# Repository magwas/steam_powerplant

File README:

An Open Hardware RISC-V based rugged, watercooled laptop with steampunk design.

Design Goals:

- based on the HiFive Unmatched Rev B board, because it is RISC-V
- actually useable
- waterproof
- shock proof
- long battery life
- water cooled
- steampunk

Not Design Goals:

- small
- lightweight

I wanted a RISC-V laptop. 
I usually carry my laptop in my car, and sometimes things happen to it.
So I choose ruggedness over lightness.
The laptop is my single most important object, so I looked up the parts I need, without regard to their price.
Well, later I added up the prices, and got a little shock.
But I have already ordered everything, so...

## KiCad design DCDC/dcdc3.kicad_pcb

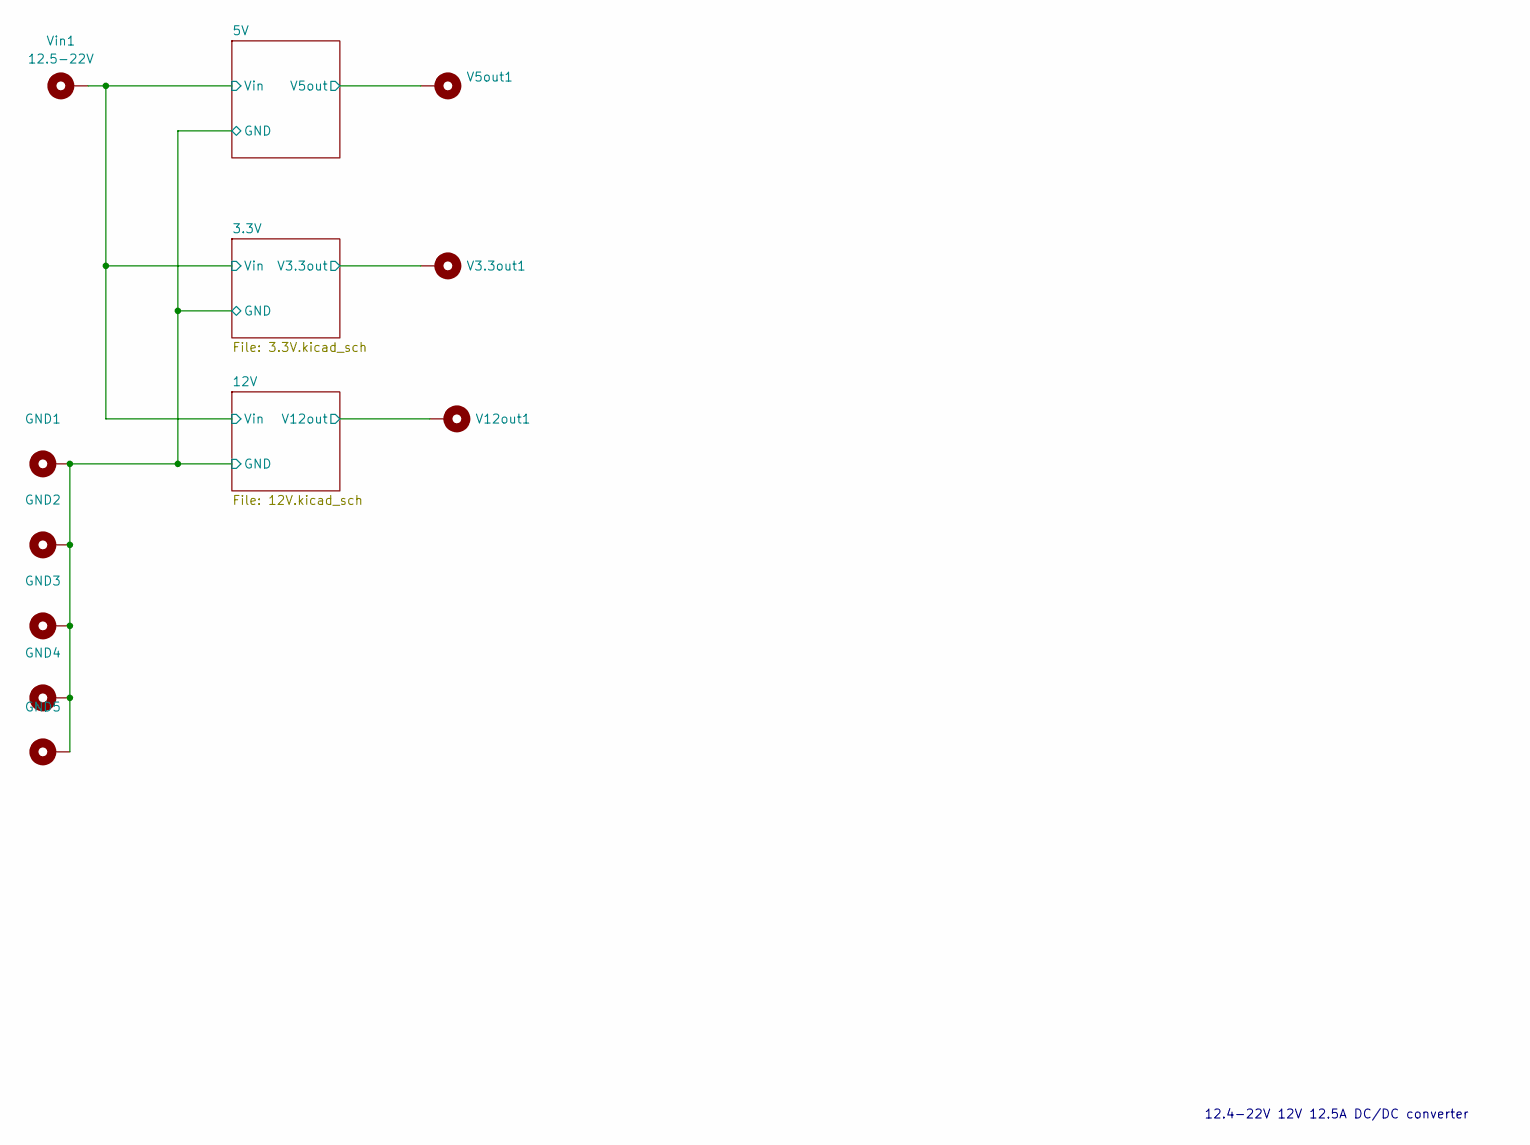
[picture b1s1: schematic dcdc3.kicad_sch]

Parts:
GND1, GND2, GND3, GND4, GND5: MountingHole_2.7mm_M2.5_Pad_Via
V3.3out1, V5out1, V12out1: MountingHole_2.7mm_M2.5_Pad_Via
Vin1: 12.5-22V; MountingHole_2.7mm_M2.5_Pad_Via

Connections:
/3.3V/V3.3out: V3.3out1.1; also elsewhere on the board
/5V/V5out: V5out1.1; also elsewhere on the board
/12V/GND: GND1.1, GND2.1, GND3.1, GND4.1, GND5.1; also elsewhere on the board
/12V/V12out: V12out1.1; also elsewhere on the board
/12V/Vin: Vin1.1; also elsewhere on the board

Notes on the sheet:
12.4-22V 12V 12.5A DC/DC converter

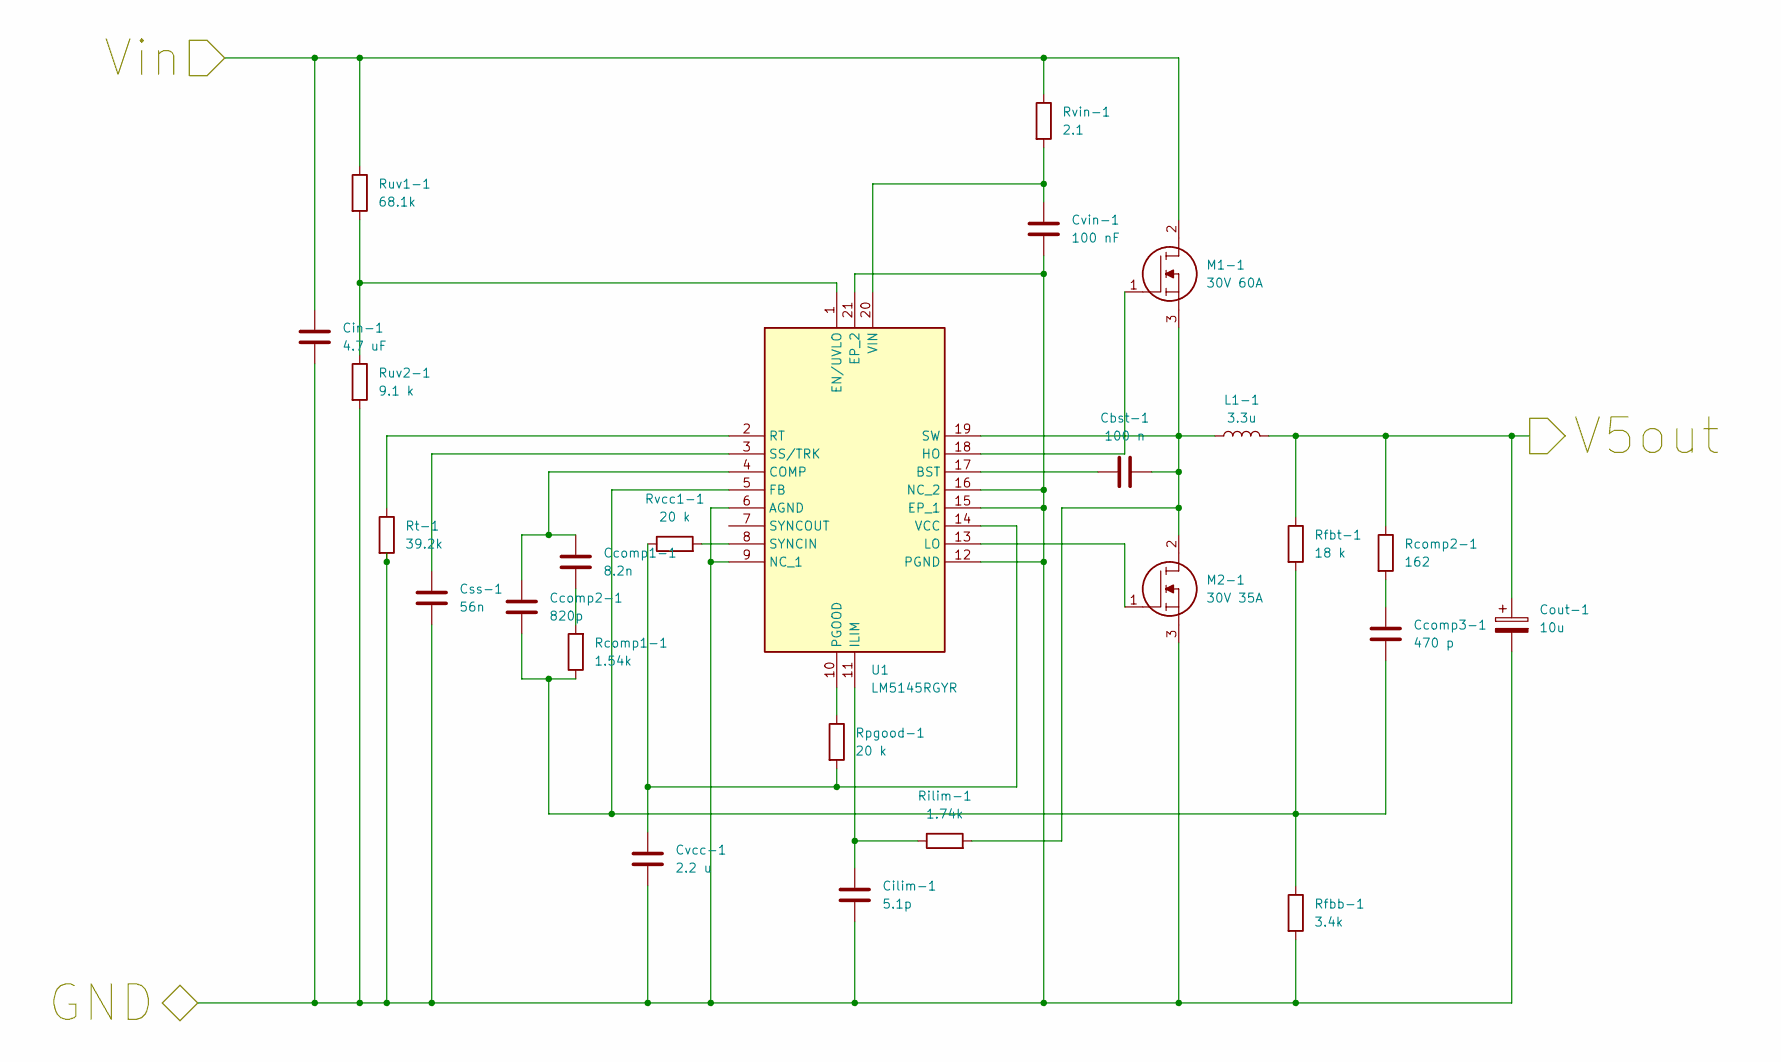
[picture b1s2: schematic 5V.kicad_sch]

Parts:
Cbst-1: 100 n; C_0603_1608Metric; Manufacturer_Part_Number C0603C104J1RACAUTO
Ccomp1-1: 8.2n; C_0402_1005Metric; Manufacturer_Part_Number GRM155R71C822KA01D
Ccomp2-1: 820p; C_0402_1005Metric; Manufacturer_Part_Number GRM155R71H821KA01D
Ccomp3-1: 470 p; C_0402_1005Metric; Manufacturer_Part_Number CGA2B2X7R1H471K050BA
Cilim-1: 5.1p; C_0805_2012Metric; Manufacturer_Part_Number C0805C519DBGACTU
Cin-1: 4.7 uF; C_1210_3225Metric; Manufacturer_Part_Number GRM32ER71H475KA88L
Cout-1: 10u; C_Radial_D10.0mm_H12.5mm_P5.00mm; Manufacturer_Part_Number KTD500B106M55A0T00
Css-1: 56n; C_0402_1005Metric; Manufacturer_Part_Number GRM155R71C563KA88D
Cvcc-1: 2.2 u; C_0402_1005Metric; Manufacturer_Part_Number C1005X5R1V225K050BC
Cvin-1: 100 nF; C_0603_1608Metric; Manufacturer_Part_Number CGA3E2X7R1H104K080AA
L1-1: 3.3u; A3mmCoil; Manufacturer_Part_Number D=15mm,N=15,L=15mm,d=2mm
M1-1: 30V 60A; TO545P521X1594X2566-3P; Mouser Part Number 747-IXFX360N10T
M2-1: 30V 35A; TO545P521X1594X2566-3P; Mouser Part Number 747-IXFX360N10T
Rcomp1-1: 1.54k; R_0402_1005Metric; Manufacturer_Part_Number CRCW04021K78FKED
Rcomp2-1: 162; R_0402_1005Metric; Manufacturer_Part_Number CRCW0402162RFKED
Rfbb-1: 3.4k; R_0402_1005Metric; Manufacturer_Part_Number CRCW04023K40FKED
Rfbt-1: 18 k; R_0603_1608Metric; Manufacturer_Part_Number RC0603FR-0718KL
Rilim-1: 1.74k; R_0402_1005Metric; Manufacturer_Part_Number CRCW04021K74FKED
Rpgood-1: 20 k; R_0603_1608Metric; Manufacturer_Part_Number RC0603FR-0720KL
Rt-1: 39.2k; R_0402_1005Metric; Manufacturer_Part_Number CRCW040239K2FKED
Ruv1-1: 68.1k; R_0603_1608Metric; Manufacturer_Part_Number ERA-3VEB6812V
Ruv2-1: 9.1 k; R_0603_1608Metric; Manufacturer_Part_Number RC0603FR-079K1L
Rvcc1-1: 20 k; R_0603_1608Metric; Manufacturer_Part_Number RC0603FR-0720KL
Rvin-1: 2.1; R_0603_1608Metric; Manufacturer_Part_Number CRCW06032R10FKEA
U1: LM5145RGYR; RGY0020B; Manufacturer_Part_Number LM5145RGYR; Mouser Part Number 595-LM5145RGYR

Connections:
/5V/V5out: Cout-1.1, L1-1.2, Rcomp2-1.1, Rfbt-1.1; also elsewhere on the board
/12V/GND: Cilim-1.2, Cin-1.2, Cout-1.2, Css-1.2, Cvcc-1.2, Cvin-1.2, M2-1.3, Rfbb-1.2, Rt-1.2, Ruv2-1.2, U1.6 (AGND), U1.9 (NC_1), U1.12 (PGND), U1.15 (EP_1), U1.16 (NC_2), U1.21 (EP_2); also elsewhere on the board
/12V/Vin: Cin-1.1, M1-1.2, Ruv1-1.1, Rvin-1.1; also elsewhere on the board
unnamed: Ccomp1-1.1, Rcomp1-1.2
unnamed: Ccomp3-1.1, Rcomp2-1.2
unnamed: Cbst-1.1, U1.17 (BST)
unnamed: Ccomp1-1.2, Ccomp2-1.2, U1.4 (COMP)
unnamed: Ruv1-1.2, Ruv2-1.1, U1.1 (EN/UVLO)
unnamed: Ccomp2-1.1, Ccomp3-1.2, Rcomp1-1.1, Rfbb-1.1, Rfbt-1.2, U1.5 (FB)
unnamed: M1-1.1, U1.18 (HO)
unnamed: Cilim-1.1, Rilim-1.1, U1.11 (ILIM)
unnamed: M2-1.1, U1.13 (LO)
unnamed: Rpgood-1.1, U1.10 (PGOOD)
unnamed: Rt-1.1, U1.2 (RT)
unnamed: Css-1.1, U1.3 (SS/TRK)
unnamed: Cbst-1.2, L1-1.1, M1-1.3, M2-1.2, Rilim-1.2, U1.19 (SW)
unnamed: Rvcc1-1.2, U1.8 (SYNCIN)
unnamed: Cvcc-1.1, Rpgood-1.2, Rvcc1-1.1, U1.14 (VCC)
unnamed: Cvin-1.1, Rvin-1.2, U1.20 (VIN)

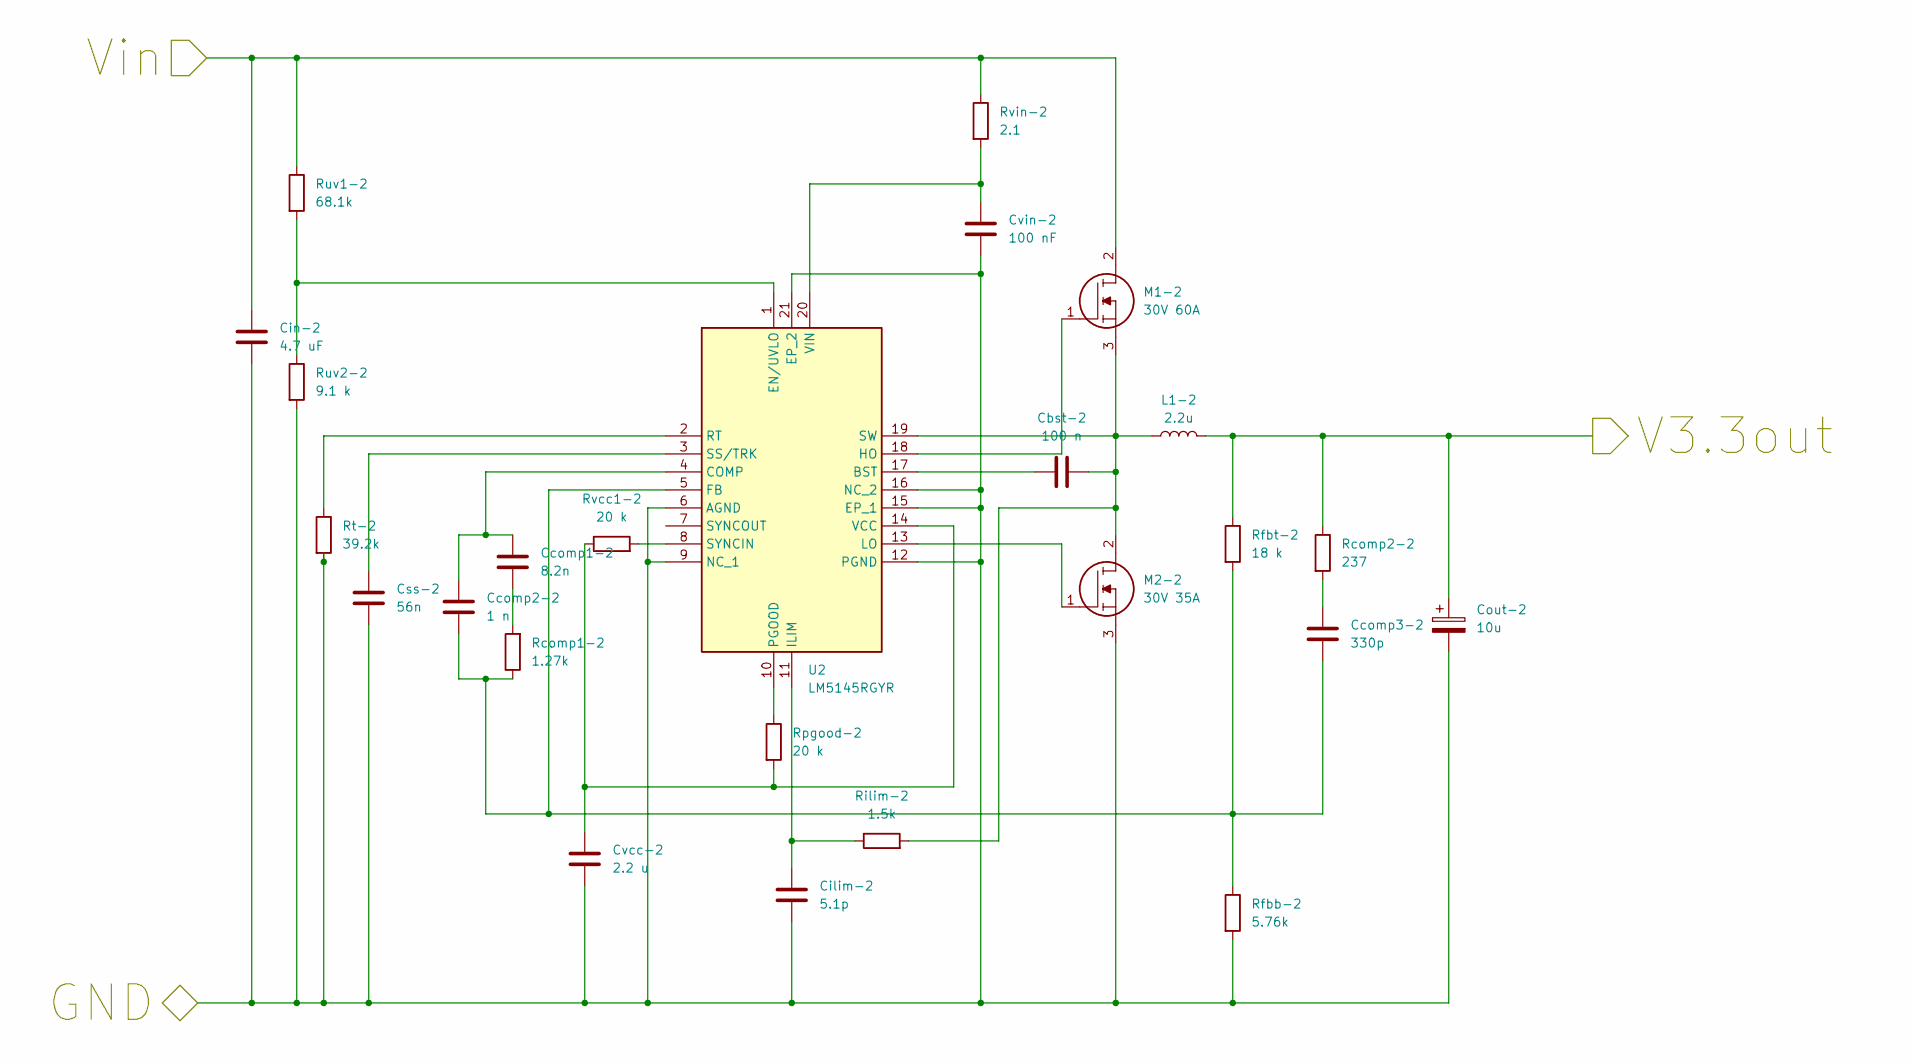
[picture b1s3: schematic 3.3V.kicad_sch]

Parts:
Cbst-2: 100 n; C_0603_1608Metric; Manufacturer_Part_Number C0603C104J1RACAUTO
Ccomp1-2: 8.2n; C_0402_1005Metric; Manufacturer_Part_Number GRM155R71C822KA01D
Ccomp2-2: 1 n; C_0402_1005Metric; Manufacturer_Part_Number GRM155R71C102KA01D
Ccomp3-2: 330p; C_0402_1005Metric; Manufacturer_Part_Number CGA2B2X7R1H331K050BA
Cilim-2: 5.1p; C_0805_2012Metric; Manufacturer_Part_Number C0805C519DBGACTU
Cin-2: 4.7 uF; C_1210_3225Metric; Manufacturer_Part_Number GRM32ER71H475KA88L
Cout-2: 10u; C_Radial_D10.0mm_H12.5mm_P5.00mm; Manufacturer_Part_Number KTD500B106M55A0T00
Css-2: 56n; C_0402_1005Metric; Manufacturer_Part_Number GRM155R71C563KA88D
Cvcc-2: 2.2 u; C_0402_1005Metric; Manufacturer_Part_Number C1005X5R1V225K050BC
Cvin-2: 100 nF; C_0603_1608Metric; Manufacturer_Part_Number CGA3E2X7R1H104K080AA
L1-2: 2.2u; A3mmCoil; Manufacturer_Part_Number D=15mm,N=10,L=20mm,d=2mm
M1-2: 30V 60A; TO545P521X1594X2566-3P; Mouser Part Number 747-IXFX360N10T
M2-2: 30V 35A; TO545P521X1594X2566-3P; Mouser Part Number 747-IXFX360N10T
Rcomp1-2: 1.27k; R_0402_1005Metric; Manufacturer_Part_Number CRCW04021K27FKED
Rcomp2-2: 237; R_0402_1005Metric; Manufacturer_Part_Number CRCW0402237RFKED
Rfbb-2: 5.76k; R_0402_1005Metric; Manufacturer_Part_Number CRCW04025K76FKED
Rfbt-2: 18 k; R_0603_1608Metric; Manufacturer_Part_Number RC0603FR-0718KL
Rilim-2: 1.5k; R_0402_1005Metric; Manufacturer_Part_Number CRCW04021K50FKED
Rpgood-2: 20 k; R_0603_1608Metric; Manufacturer_Part_Number RC0603FR-0720KL
Rt-2: 39.2k; R_0402_1005Metric; Manufacturer_Part_Number CRCW040239K2FKED
Ruv1-2: 68.1k; R_0603_1608Metric; Manufacturer_Part_Number ERA-3VEB6812V
Ruv2-2: 9.1 k; R_0603_1608Metric; Manufacturer_Part_Number RC0603FR-079K1L
Rvcc1-2: 20 k; R_0603_1608Metric; Manufacturer_Part_Number RC0603FR-0720KL
Rvin-2: 2.1; R_0603_1608Metric; Manufacturer_Part_Number CRCW06032R10FKEA
U2: LM5145RGYR; RGY0020B; Manufacturer_Part_Number LM5145RGYR; Mouser Part Number 595-LM5145RGYR

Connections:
/3.3V/V3.3out: Cout-2.1, L1-2.2, Rcomp2-2.1, Rfbt-2.1; also elsewhere on the board
/12V/GND: Cilim-2.2, Cin-2.2, Cout-2.2, Css-2.2, Cvcc-2.2, Cvin-2.2, M2-2.3, Rfbb-2.2, Rt-2.2, Ruv2-2.2, U2.6 (AGND), U2.9 (NC_1), U2.12 (PGND), U2.15 (EP_1), U2.16 (NC_2), U2.21 (EP_2); also elsewhere on the board
/12V/Vin: Cin-2.1, M1-2.2, Ruv1-2.1, Rvin-2.1; also elsewhere on the board
unnamed: Ccomp1-2.1, Rcomp1-2.2
unnamed: Ccomp3-2.1, Rcomp2-2.2
unnamed: Cbst-2.1, U2.17 (BST)
unnamed: Ccomp1-2.2, Ccomp2-2.2, U2.4 (COMP)
unnamed: Ruv1-2.2, Ruv2-2.1, U2.1 (EN/UVLO)
unnamed: Ccomp2-2.1, Ccomp3-2.2, Rcomp1-2.1, Rfbb-2.1, Rfbt-2.2, U2.5 (FB)
unnamed: M1-2.1, U2.18 (HO)
unnamed: Cilim-2.1, Rilim-2.1, U2.11 (ILIM)
unnamed: M2-2.1, U2.13 (LO)
unnamed: Rpgood-2.1, U2.10 (PGOOD)
unnamed: Rt-2.1, U2.2 (RT)
unnamed: Css-2.1, U2.3 (SS/TRK)
unnamed: Cbst-2.2, L1-2.1, M1-2.3, M2-2.2, Rilim-2.2, U2.19 (SW)
unnamed: Rvcc1-2.2, U2.8 (SYNCIN)
unnamed: Cvcc-2.1, Rpgood-2.2, Rvcc1-2.1, U2.14 (VCC)
unnamed: Cvin-2.1, Rvin-2.2, U2.20 (VIN)

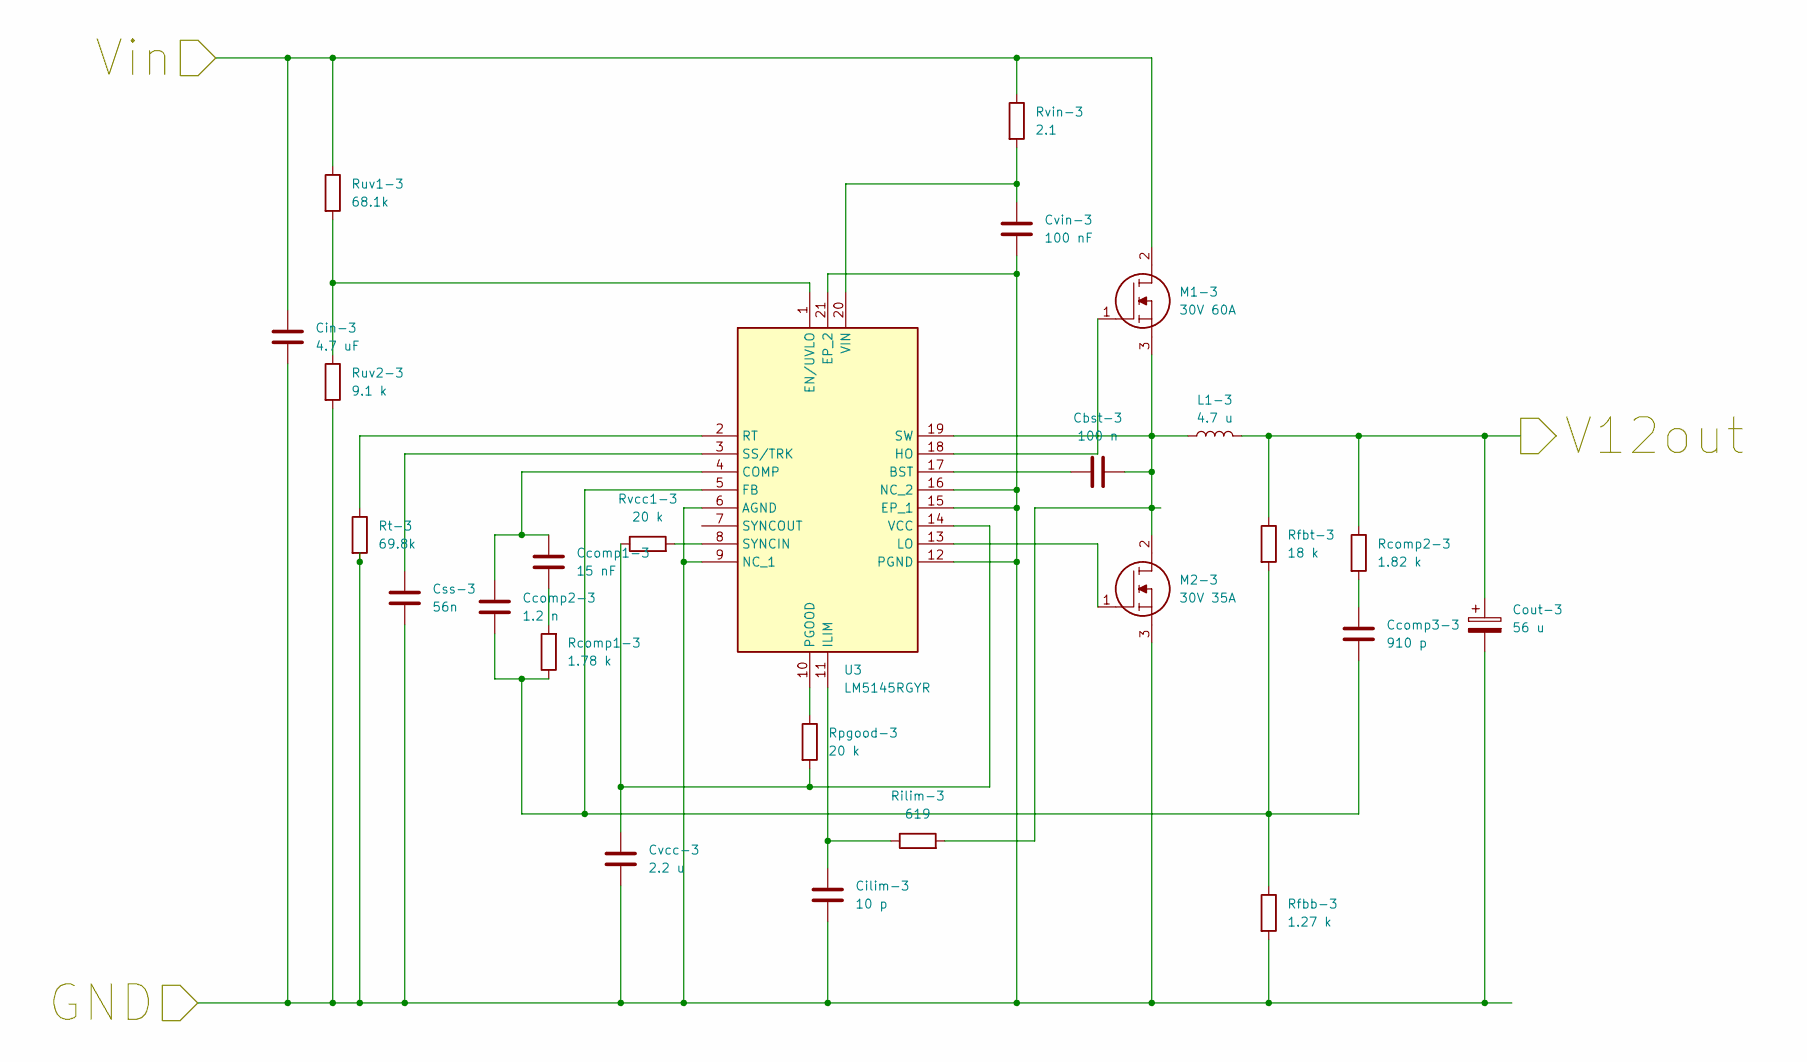
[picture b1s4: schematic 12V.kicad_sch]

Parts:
Cbst-3: 100 n; C_0603_1608Metric; Manufacturer_Part_Number C0603C104J1RACAUTO
Ccomp1-3: 15 nF; C_0402_1005Metric; Manufacturer_Part_Number GRM155R71C153KA01D
Ccomp2-3: 1.2 n; C_0402_1005Metric; Manufacturer_Part_Number GRM155R71H122KA01D
Ccomp3-3: 910 p; C_0402_1005Metric; Manufacturer_Part_Number GRM1555C1H911JA01D
Cilim-3: 10 p; C_0603_1608Metric; Manufacturer_Part_Number GRM1885C2A100JA01D
Cin-3: 4.7 uF; C_1210_3225Metric; Manufacturer_Part_Number GRM32ER71H475KA88L
Cout-3: 56 u; C_Radial_D6.3mm_H5.0mm_P2.50mm; Manufacturer_Part_Number APSG250ELL560MF05S
Css-3: 56n; C_0402_1005Metric; Manufacturer_Part_Number GRM155R71C563KA88D
Cvcc-3: 2.2 u; C_0402_1005Metric; Manufacturer_Part_Number C1005X5R1V225K050BC
Cvin-3: 100 nF; C_0603_1608Metric; Manufacturer_Part_Number CGA3E2X7R1H104K080AA
L1-3: 4.7 u; A3mmCoil; Manufacturer_Part_Number D=15mm,N=20,L=20mm,d=2mm
M1-3: 30V 60A; TO545P521X1594X2566-3P; Mouser Part Number 747-IXFX360N10T
M2-3: 30V 35A; TO545P521X1594X2566-3P; Mouser Part Number 747-IXFX360N10T
Rcomp1-3: 1.78 k; R_0402_1005Metric; Manufacturer_Part_Number CRCW04021K78FKED
Rcomp2-3: 1.82 k; R_0402_1005Metric; Manufacturer_Part_Number CRCW04021K82FKED
Rfbb-3: 1.27 k; R_0402_1005Metric; Manufacturer_Part_Number CRCW04021K27FKED
Rfbt-3: 18 k; R_0603_1608Metric; Manufacturer_Part_Number RC0603FR-0718KL
Rilim-3: 619; R_0402_1005Metric; Manufacturer_Part_Number CRCW0402619RFKED
Rpgood-3: 20 k; R_0603_1608Metric; Manufacturer_Part_Number RC0603FR-0720KL
Rt-3: 69.8k; R_0402_1005Metric; Manufacturer_Part_Number CRCW040269K8FKED
Ruv1-3: 68.1k; R_0603_1608Metric; Manufacturer_Part_Number ERA-3VEB6812V
Ruv2-3: 9.1 k; R_0603_1608Metric; Manufacturer_Part_Number RC0603FR-079K1L
Rvcc1-3: 20 k; R_0603_1608Metric; Manufacturer_Part_Number RC0603FR-0720KL
Rvin-3: 2.1; R_0603_1608Metric; Manufacturer_Part_Number CRCW06032R10FKEA
U3: LM5145RGYR; RGY0020B; Manufacturer_Part_Number LM5145RGYR; Mouser Part Number 595-LM5145RGYR

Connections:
/12V/GND: Cilim-3.2, Cin-3.2, Cout-3.2, Css-3.2, Cvcc-3.2, Cvin-3.2, M2-3.3, Rfbb-3.2, Rt-3.2, Ruv2-3.2, U3.6 (AGND), U3.9 (NC_1), U3.12 (PGND), U3.15 (EP_1), U3.16 (NC_2), U3.21 (EP_2); also elsewhere on the board
/12V/V12out: Cout-3.1, L1-3.2, Rcomp2-3.1, Rfbt-3.1; also elsewhere on the board
/12V/Vin: Cin-3.1, M1-3.2, Ruv1-3.1, Rvin-3.1; also elsewhere on the board
unnamed: Ccomp1-3.1, Rcomp1-3.2
unnamed: Ccomp3-3.1, Rcomp2-3.2
unnamed: Cbst-3.1, U3.17 (BST)
unnamed: Ccomp1-3.2, Ccomp2-3.2, U3.4 (COMP)
unnamed: Ruv1-3.2, Ruv2-3.1, U3.1 (EN/UVLO)
unnamed: Ccomp2-3.1, Ccomp3-3.2, Rcomp1-3.1, Rfbb-3.1, Rfbt-3.2, U3.5 (FB)
unnamed: M1-3.1, U3.18 (HO)
unnamed: Cilim-3.1, Rilim-3.1, U3.11 (ILIM)
unnamed: M2-3.1, U3.13 (LO)
unnamed: Rpgood-3.1, U3.10 (PGOOD)
unnamed: Rt-3.1, U3.2 (RT)
unnamed: Css-3.1, U3.3 (SS/TRK)
unnamed: Cbst-3.2, L1-3.1, M1-3.3, M2-3.2, Rilim-3.2, U3.19 (SW)
unnamed: Rvcc1-3.2, U3.8 (SYNCIN)
unnamed: Cvcc-3.1, Rpgood-3.2, Rvcc1-3.1, U3.14 (VCC)
unnamed: Cvin-3.1, Rvin-3.2, U3.20 (VIN)

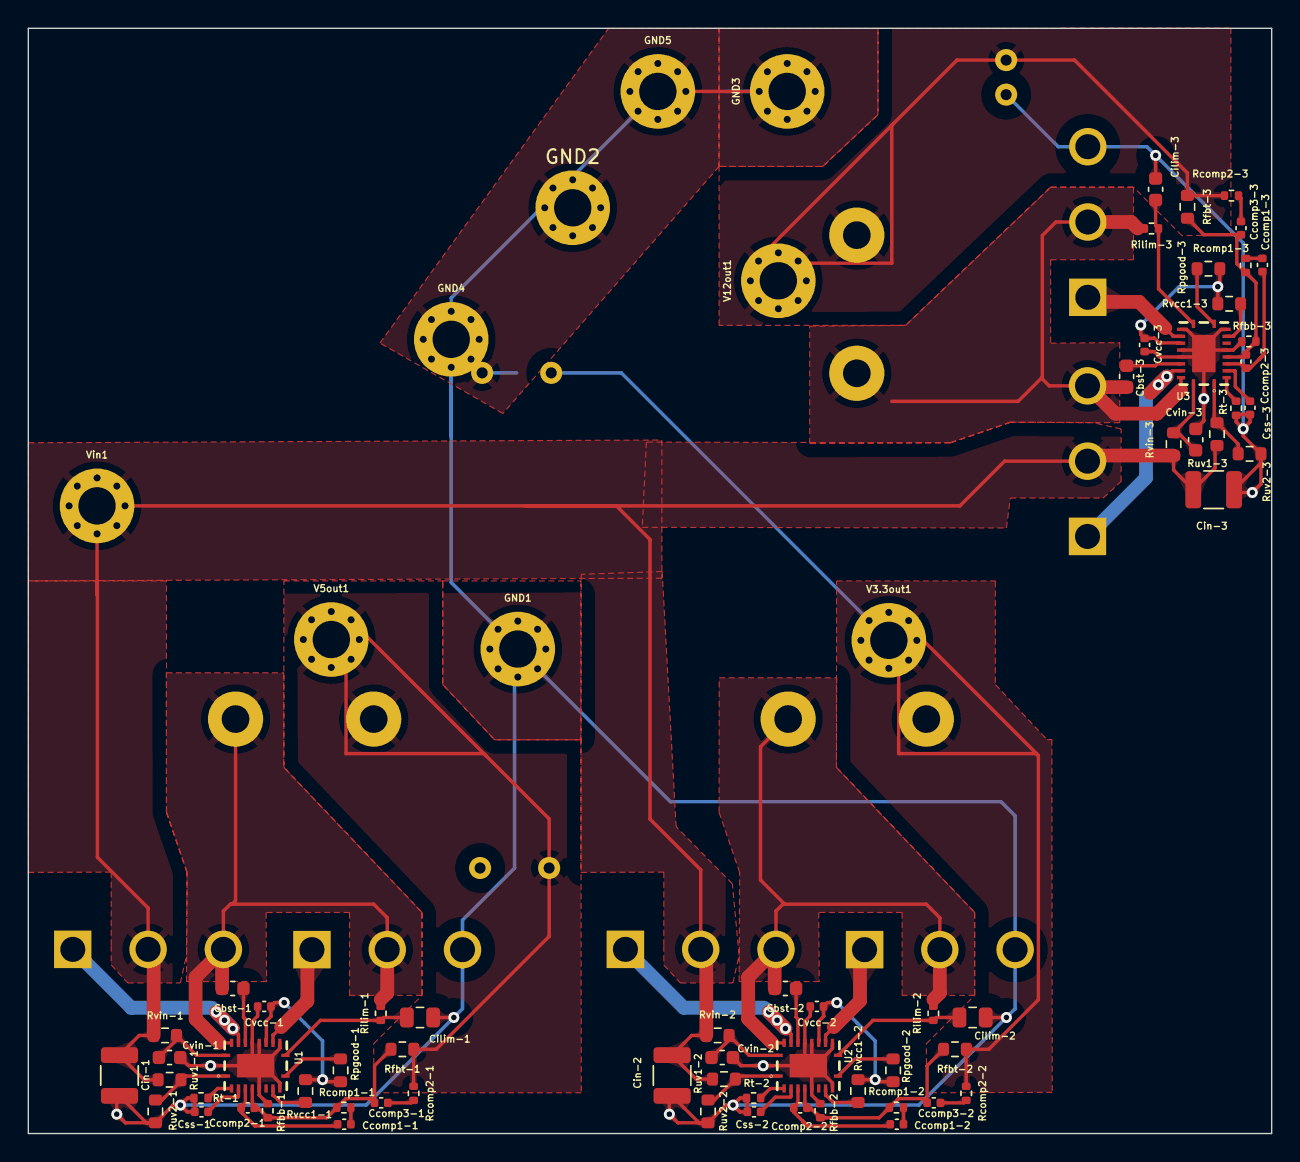
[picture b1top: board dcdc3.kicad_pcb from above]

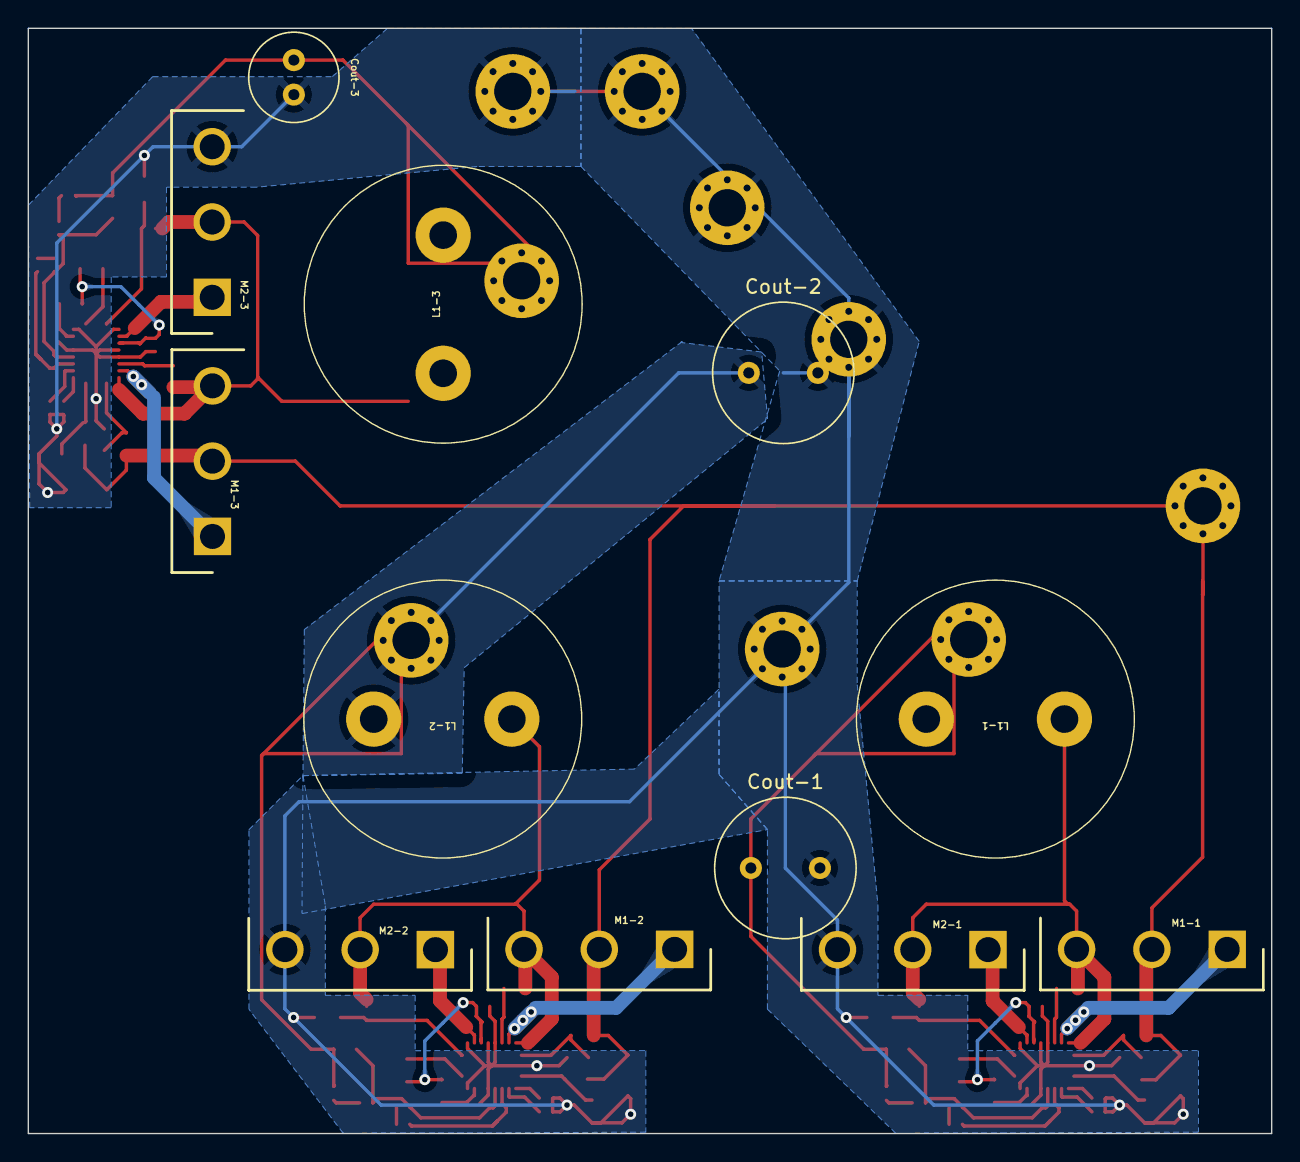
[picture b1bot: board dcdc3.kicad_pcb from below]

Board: 2 copper layers, 90.0 x 80.0 mm, 84 parts (12 on the bottom side), 53 nets.

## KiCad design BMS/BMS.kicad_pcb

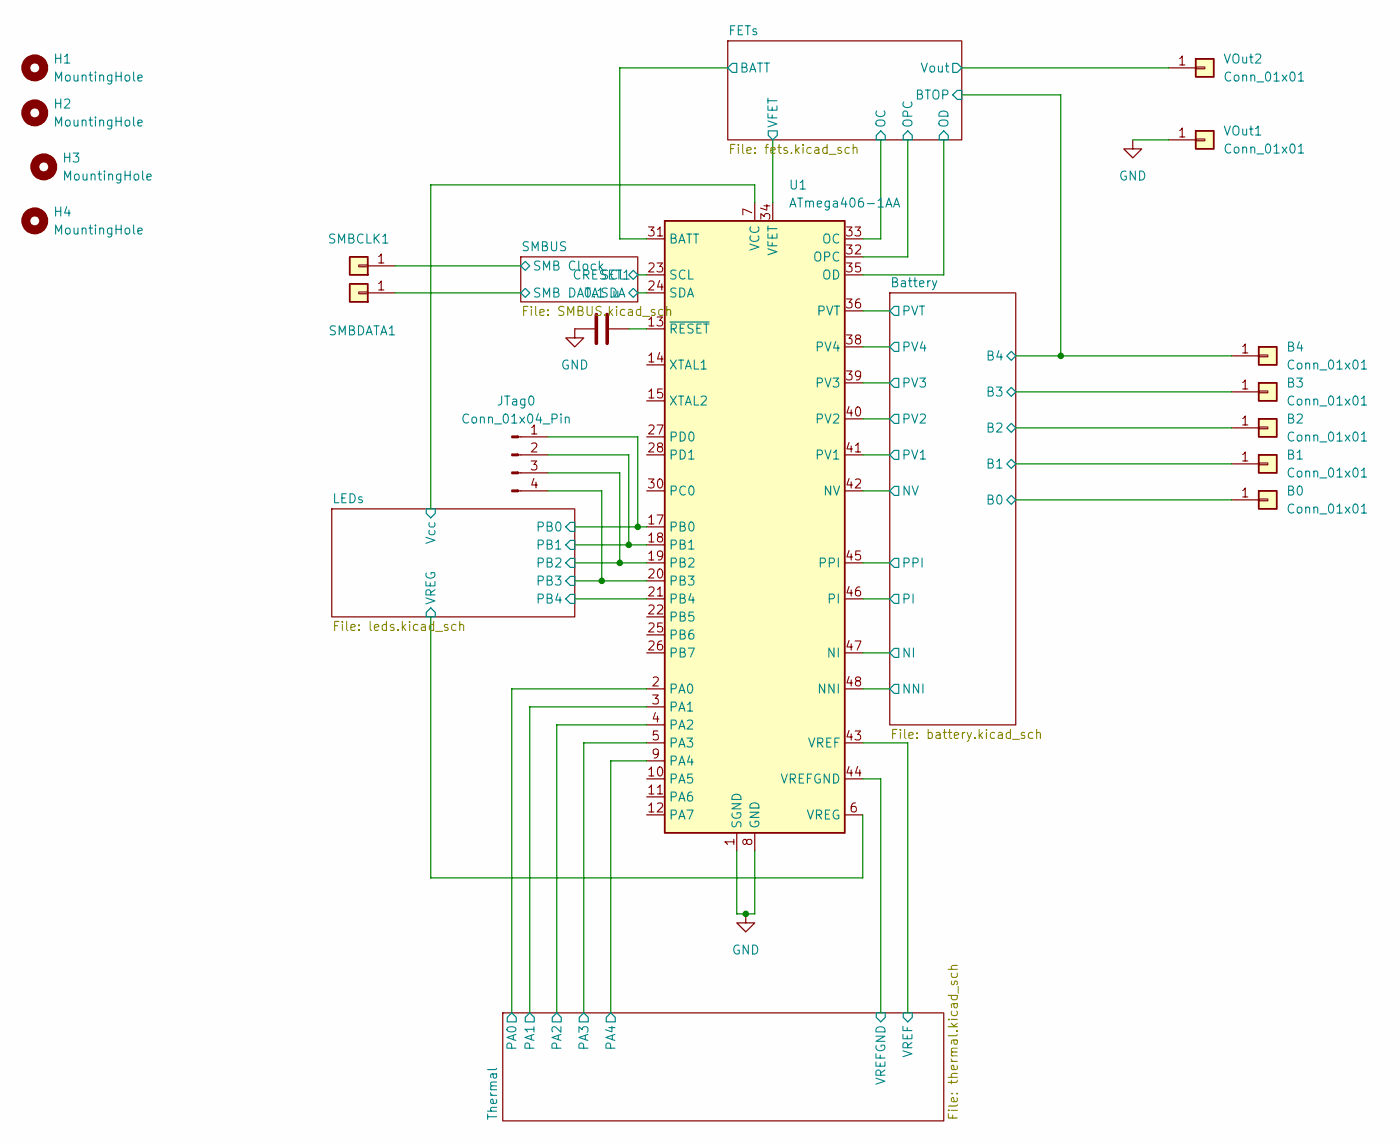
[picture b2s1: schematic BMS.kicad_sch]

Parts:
B0, B1, B2, B3, B4: Conn_01x01; SolderWire-0.1sqmm_1x01_D0.4mm_OD1mm
CRESET1: 0.1 u; C_0603_1608Metric; Manufacturer_Part_Number KAM15AR71H104KT
H1, H2, H3, H4: MountingHole; MountingHole_2.2mm_M2
JTag0: Conn_01x04_Pin; PinHeader_1x04_P2.00mm_Horizontal
SMBCLK1: Conn_01x01; SolderWire-0.1sqmm_1x01_D0.4mm_OD1mm
SMBDATA1: Conn_01x01; SolderWire-0.1sqmm_1x01_D0.4mm_OD1mm
U1: ATmega406-1AA; LQFP-48_7x7mm_P0.5mm; Manufacturer_Part_Number ATmega406-1AA
VOut1, VOut2: Conn_01x01; SolderWire-0.1sqmm_1x01_D0.4mm_OD1mm

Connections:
/Battery/B0: B0.1; also elsewhere on the board
/Battery/B1: B1.1; also elsewhere on the board
/Battery/B2: B2.1; also elsewhere on the board
/Battery/B3: B3.1; also elsewhere on the board
/Battery/B4: B4.1; also elsewhere on the board
/Battery/NI: U1.47 (NI); also elsewhere on the board
/Battery/NNI: U1.48 (NNI); also elsewhere on the board
/Battery/NV: U1.42 (NV); also elsewhere on the board
/Battery/PI: U1.46 (PI); also elsewhere on the board
/Battery/PPI: U1.45 (PPI); also elsewhere on the board
/Battery/PV1: U1.41 (PV1); also elsewhere on the board
/Battery/PV2: U1.40 (PV2); also elsewhere on the board
/Battery/PV3: U1.39 (PV3); also elsewhere on the board
/Battery/PV4: U1.38 (PV4); also elsewhere on the board
/Battery/PVT: U1.36 (PVT); also elsewhere on the board
/FETs/BATT: U1.31 (BATT); also elsewhere on the board
/FETs/OC: U1.33 (OC); also elsewhere on the board
/FETs/OD: U1.35 (OD); also elsewhere on the board
/FETs/OPC: U1.32 (OPC); also elsewhere on the board
/FETs/VFET: U1.34 (VFET); also elsewhere on the board
/FETs/Vout: VOut2.1; also elsewhere on the board
/LEDs/PB0: JTag0.1, U1.17 (PB0); also elsewhere on the board
/LEDs/PB1: JTag0.2, U1.18 (PB1); also elsewhere on the board
/LEDs/PB2: JTag0.3, U1.19 (PB2); also elsewhere on the board
/LEDs/PB3: JTag0.4, U1.20 (PB3); also elsewhere on the board
/LEDs/PB4: U1.21 (PB4); also elsewhere on the board
/LEDs/VREG: U1.6 (VREG), U1.7 (VCC); also elsewhere on the board
/SMBUS/SCL: SMBCLK1.1, U1.23 (SCL); also elsewhere on the board
/SMBUS/SDA: SMBDATA1.1, U1.24 (SDA); also elsewhere on the board
/Thermal/PA0: U1.2 (PA0); also elsewhere on the board
/Thermal/PA1: U1.3 (PA1); also elsewhere on the board
/Thermal/PA2: U1.4 (PA2); also elsewhere on the board
/Thermal/PA3: U1.5 (PA3); also elsewhere on the board
/Thermal/PA4: U1.9 (PA4); also elsewhere on the board
/Thermal/VREF: U1.43 (VREF); also elsewhere on the board
/Thermal/VREFGND: U1.44 (VREFGND); also elsewhere on the board
GND: CRESET1.1, U1.1 (SGND), U1.8 (GND), U1.16 (GND), U1.29 (GND), U1.37 (GND), VOut1.1; also elsewhere on the board
unnamed: CRESET1.2, U1.13 (~RESET)

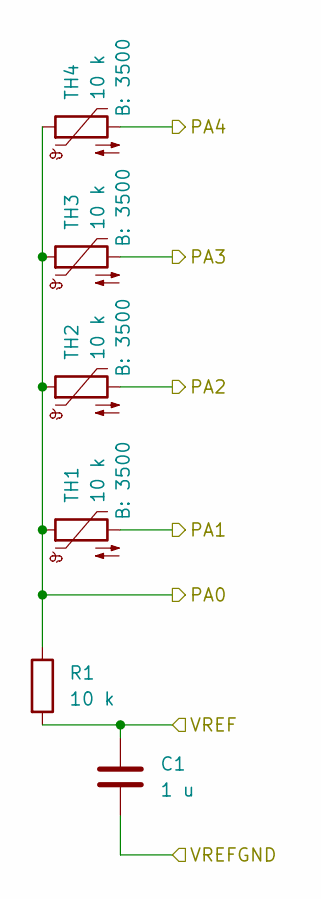
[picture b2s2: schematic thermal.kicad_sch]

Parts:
C1: 1 u; C_0805_2012Metric; Manufacturer_Part_Number KGM21AR71H105JU
R1: 10 k; R_0402_1005Metric; Manufacturer_Part_Number CRCW040210K0FKEDC
TH1, TH2, TH3, TH4: 10 k; R_Axial_DIN0204_L3.6mm_D1.6mm_P1.90mm_Vertical; Manufacturer_Part_Number 214650-1633

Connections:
/Thermal/PA0: R1.1, TH1.1, TH2.1, TH3.1, TH4.1; also elsewhere on the board
/Thermal/PA1: TH1.2; also elsewhere on the board
/Thermal/PA2: TH2.2; also elsewhere on the board
/Thermal/PA3: TH3.2; also elsewhere on the board
/Thermal/PA4: TH4.2; also elsewhere on the board
/Thermal/VREF: C1.1, R1.2; also elsewhere on the board
/Thermal/VREFGND: C1.2; also elsewhere on the board

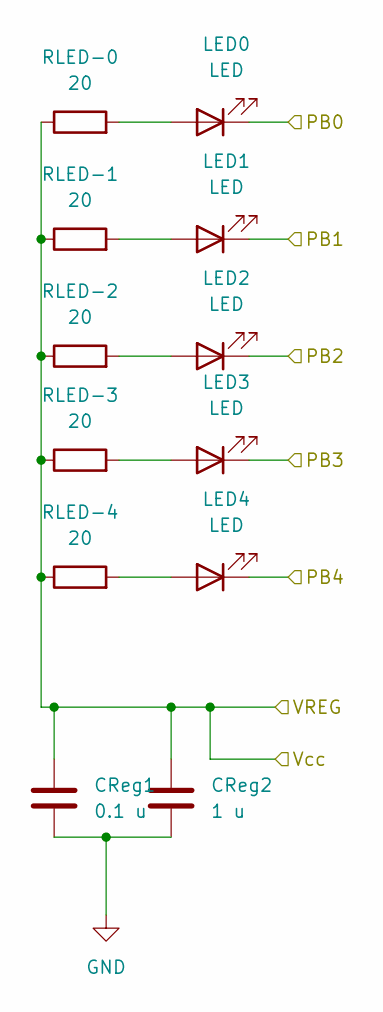
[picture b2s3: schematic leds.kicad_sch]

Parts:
CReg1: 0.1 u; C_0603_1608Metric; Manufacturer_Part_Number KAM15AR71H104KT
CReg2: 1 u; C_0805_2012Metric; Manufacturer_Part_Number KGM21AR71H105JU
LED0, LED1, LED2, LED3, LED4: LED; D_0603_1608Metric; Manufacturer_Part_Number ASCKCA00-BU4V4020502
RLED-0, RLED-1, RLED-2, RLED-3, RLED-4: 20; R_0402_1005Metric; Manufacturer_Part_Number ESR01MZPF20R0

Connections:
/LEDs/PB0: LED0.1 (K); also elsewhere on the board
/LEDs/PB1: LED1.1 (K); also elsewhere on the board
/LEDs/PB2: LED2.1 (K); also elsewhere on the board
/LEDs/PB3: LED3.1 (K); also elsewhere on the board
/LEDs/PB4: LED4.1 (K); also elsewhere on the board
/LEDs/VREG: CReg1.1, CReg2.1, RLED-0.1, RLED-1.1, RLED-2.1, RLED-3.1, RLED-4.1; also elsewhere on the board
GND: CReg1.2, CReg2.2; also elsewhere on the board
unnamed: LED0.2 (A), RLED-0.2
unnamed: LED1.2 (A), RLED-1.2
unnamed: LED2.2 (A), RLED-2.2
unnamed: LED3.2 (A), RLED-3.2
unnamed: LED4.2 (A), RLED-4.2
